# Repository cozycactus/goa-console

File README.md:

# goa-console

A DIY line-level mixing console with 24 or more channels, in the style of the Soundcraft Delta and meant for mixing
hardware synths (goa trance). It is designed in KiCad. Python generates the schematics, which are checked against
intended netlists and simulated in ngspice.

> **Design only, not built.** No board here has been routed, fabricated or powered, so nothing is proven on the bench.
> The external PSU connects to mains, so build it only if you are qualified to work with mains voltages. See
> [Licence](#licence): there is no warranty of any kind.

*3D model built from the placed KiCad boards (`tools/console_3d.py`). Knob caps and panel finish are placeholders.*

## What it is

- **Modules on a motherloom.** Each channel is a Delta Theatre input without the mic stage:
  - one 8 HP × 12U panel with two boards: a 38 × 400 mm main board and a 38 × 43 mm jack board;
  - every module plugs into a daisy-chained 34-way IDC ribbon that uses the Delta's own motherloom pinout, one ribbon
    per wing of 12 strips;
  - the 16 HP master module sits in the centre with both wing headers and the power entry; the four 8 HP group
    modules sit next to it, two on each wing.
- **Channel strip** (spec v5.7):
  - a buffered differential line receiver (OPA1656 followers) and an inverting line gain stage, −15…+15 dB with a
    centre detent;
  - a Ø switch and a sweepable 21–403 Hz high-pass filter (KHN);
  - the Delta's four-band EQ, except that the two swept mid bands are rebuilt as KHN state-variable band-pass
    filters, so a stocked A10K dual pot tunes them;
  - an insert after the EQ, ON (a JFET soft mute that also mutes the pre-fade sends and the direct out) and PFL;
  - a 100 mm fader with a +10 dB post-amp, then pan and routing to L-R, 1-2 and 3-4 through DG413 switches at the
    bus end of each 4K7 summing resistor;
  - six aux sends, with one PRE switch per pair of sends (solder jumpers pick its source: pre-fader or pre-EQ) and a
    DIR switch that makes the aux 6 pot the level of the direct out.
- **Master:**
  - mix summing referenced to a ground-cancel line, each sum followed by a re-inverter;
  - DRV135UA (DRV134 family) balanced outputs with mute relays, plus a power-on mute;
  - mono, PFL and AFL monitoring, 20-LED meters on each side, and the masters for aux 5 and 6.
- **Groups:** each has a sub bus with insert and pan, two stereo returns and an aux master (aux n on group n).
- **Power:** an external supply giving ±17 V at 4 A per rail. Two isolated Mean Well LRS-150-24 modules each feed a
  floating rail with its own LC filter, LM1084 regulator and SCR crowbar. A 7-pin XLR carries the supply to the
  console.

<table>
<tr>
<td></td>
</tr>
<tr>
<td><em>Strip panel print in the Delta's style</em></td>
</tr>
</table>

## Status

| Part | Schematic | Placement | Routing |
|------|-----------|-----------|---------|
| Channel strip (main + jack board) | done, verified, simulated | done | to do |
| Group module ×4 (main + jack board) | done, verified | done | to do |
| Master module (main + jack board) | done, verified | done | to do |
| External PSU | done, verified, simulated | done | to do |
| Test jig (master stub + load board) | done, verified | done | to do |

- **Component placement only.** The boards are generated by the placer and carry no tracks, vias or zones; copper
  routing is done by hand in KiCad (see `AGENTS.md`). Unrouted connections are expected.
- **What the checks show:**
  - parity DRC finds 0 schematic-parity issues on every board;
  - the strip, group and master main boards and both jig boards have 0 DRC violations;
  - the jack boards report only items inside KiCad's NJ6FD-V footprint, and the PSU only 20 known TO-220 silk-edge
    items (the tabs overhang the board edge by design);
  - `python3 tools/check_all.py` runs every check in one go (netlist against intended, pins against footprints, ERC,
    parity DRC, footprint links, route_check, the simulations and the rule tests) and exits non-zero on any failure.
- **Still open:**
  - the bench checks from the master parts review (`docs/reviews/master_parts_review.md`, signed off and applied 2026-10-23):
    re-inverter stability, aux noise, relay release and mains-off timing, PFL tick, meter current-source temperature;
  - check the panel parts against samples:
    - fader pad pattern (1:1 print) and which side of the slot the pins sit;
    - fader law, which the printed dB scale needs;
    - fader-cap fit on the blade;
    - panel stack height;
    - PV cap clearance;
    - knob fit;
  - check the pan pot (ALPS RK09L1240015, chosen 2026-10-25) and the PVA2 latch orientation on samples;
  - route the boards;
  - build the test jig with four routed strips and run its bus tests (`test_jig_spec.md`); some bus decisions wait on
    them;
  - build the 12U frame (`frame/`, FR1-FR3) and the PSU case (`psu_case/`, PC1-PC3: Hammond 1402KV, Fischer SK 47 75 SA).

  The details are in `CLAUDE.md`, "Not done / open" and "Next steps".

## Repository layout

| Path | What |
|------|------|
| `console_architecture.md` | Whole-console architecture (authoritative): bus pinout, grounding, power, op-amp choices |
| `channel_strip_schematic_spec.md`, `docs/reviews/strip_parts_review.md` | Strip component-level spec v5.7 (authoritative), including panel parts and stack (§16); the stability and ratings review behind v4.1 |
| `master_section_spec.md`, `docs/studies/master_panel_study.md`, `docs/reviews/master_parts_review.md` | Master and group modules: functions, parts, panel study, review of the proposed parts |
| `psu_spec.md`, `test_jig_spec.md` | External PSU, test jig |
| `docs/studies/delta_clone_comparison.md`, `docs/studies/strip_panel_study.md` | Why the strip is a Delta clone, why 8 HP × 12U with two pot columns |
| `docs/build/panel_parts_drawings.md`, `docs/build/panel_print.md` | Panel parts against their manufacturers' drawings; the Delta's panel legend system and ours |
| `boards/<name>/` | One folder per KiCad project, nine in all (`channel_strip`, `jack_board`, `group`, `group_jack_board`, `master`, `master_jack_board`, `jig_master_stub`, `jig_load_board`, `psu`). Each holds the generated schematic (`.kicad_sch`, with `*_sheets/` for the hierarchical ones) and placed board (`.kicad_pcb`), `.kicad_pro`, `.kicad_dru`, the netlist `.net`, `_intended.json`, and its own `fp-lib-table` / `sym-lib-table` pointing at the project libraries in the repository root |
| `boards/channel_strip/` | The strip's main board: `channel_strip.kicad_pro` opens it with the schematic. The old v3.1 board is `archive/channel_strip_v3.1.kicad_pcb` |
| `docs/` | The design record: `proposals/`, `reviews/`, `studies/`, `build/` (sourcing, samples, escape plan, panel print), `decisions.md`, `verification_log.md`, `tooling.md`, and `INDEX.md`, the map of all of it |
| `pdf/*.pdf`, `bom/*_BOM.csv` | Schematic PDF and BOM exports; `bom/` also holds the order lists. The netlists (`.net`) and `*_intended.json`, the netlists the schematics are checked against, live in each board's folder |
| `goa-console.pretty/`, `goa-console.3dshapes/`, `goa-console.kicad_sym` | Project footprints (faders, spade tab, PTC), part 3D models (VRML + STEP), symbols |
| `tools/` | Generators, verification (`check_all.py` runs everything), placement engine, routing rules (`netrules.py`), fab outputs (`fab_out.py`), the order list (`order_bom.py`), 3D export and Blender build (below) |
| `sim/` | ngspice decks and Python sims: signal path, EQ, gain stage, mid tuning, routing switch, master mix, meters, mute, PSU |
| `ref/` | **Not in this repository.** It holds third-party documents: the Soundcraft Delta DLX/Theatre schematics, the 200 Delta Technical Manual and User Guide with panel-drawing crops, the Mackie 1604-VLZ service manual and an API 500 spec. The docs still cite them by their `ref/...` paths. The folder is git-ignored, so a local copy stays out of commits |
| `render/` | 3D exports (`*.json`); renders and the `.blend` are generated and git-ignored |
| `CLAUDE.md` | Working notes: rules, current state, one-line decisions, open items; the detail in `docs/INDEX.md` (file map, proposals table), `docs/tooling.md`, `docs/decisions.md` (decisions in full), `docs/verification_log.md` |

## Toolchain

- KiCad 10.0.7: `kicad-cli`, plus its bundled Python 3.9 for `pcbnew` (placement and 3D export).
- Python 3 with a `.venv` holding kiutils 1.4.8 (the schematic generators).
- ngspice 46.
- Blender 5.2, optional (3D model and renders).

On macOS:

```bash
KC=/Applications/KiCad/KiCad.app/Contents/MacOS/kicad-cli
KPY=/Applications/KiCad/KiCad.app/Contents/Frameworks/Python.framework/Versions/3.9/bin/python3
python3 -m venv .venv && .venv/bin/pip install kiutils==1.4.8
```

## Working on it

The schematics are generated: edit the generator, then regenerate and verify every schematic it writes. For the
strip:

```bash
# writes boards/channel_strip/channel_strip.kicad_sch and boards/jack_board/jack_board.kicad_sch
.venv/bin/python tools/gen.py boards/channel_strip/channel_strip.kicad_sch
for s in channel_strip jack_board; do
  $KC sch export netlist -o $s.net $s.kicad_sch
  .venv/bin/python tools/verify.py $s.net ${s}_intended.json
  # symbol pins vs footprint pads
  python3 tools/check_fp.py $s.net
  $KC sch erc --severity-all $s.kicad_sch
done
# strip only: both netlists joined by the ribbon, simulated in ngspice
python3 tools/sim_netlist.py boards/channel_strip/channel_strip.net boards/jack_board/jack_board.net
```

The whole console (24 strips, 4 groups and the master, each with its jack board, on the ribbon) is simulated from the
generated netlists with `python3 tools/sim_console.py` (108 checks, a little over a minute; `--list` names them). It covers
levels, routing, mutes, PFL, returns, EXT, crosstalk, ground currents and noise. Regenerate the netlists first.

The other generators work the same way:

| Generator | Writes |
|-----------|--------|
| `gen_group.py boards/group/group.kicad_sch` | group, group_jack_board |
| `gen_master.py boards/master/master.kicad_sch` | master, master_jack_board |
| `gen_psu.py` (no argument) | psu |
| `gen_jig.py` (no argument) | jig_master_stub, jig_load_board |

Run the export / verify / check_fp / ERC steps for each schematic in the right-hand column.

Simulations: each deck in `sim/` runs its own analyses, e.g. `ngspice -b sim/strip_v4.cir` (the v4.0 strip model; the
current strip is checked from its netlist by `sim_netlist.py`, 45 checks). `python3 sim/mid_tuning.py 10e3` compares the
mid-band tunings for a given pot value (the 2026-10-22 tuning; the v5.5 ranges come from `sim/review/eqmid/measure.py`).

Placement only. The strip, group and master main boards have four layers, with a solid ground plane and a ground fill
inside (`docs/studies/layer_study.md`); every other board has two. Each script refuses to overwrite a board that
already has routing:

```bash
# strip main board + jack board
tools/build_strip_pcb.sh
# group, master (~3 min) and their jack boards
$KPY tools/place_group.py
$KPY tools/place_master.py
$KPY tools/place_jig.py
$KPY tools/place_psu.py
```

Each run prints a placement report: decoupler-to-supply-pin distances and the reach of high-impedance input
networks. Every board is its schematic's project board, so parity DRC runs in place
(`$KC pcb drc --schematic-parity --severity-all X.kicad_pcb`). After any re-placement or netlist change, re-run
`$KPY tools/netrules.py` (net classes and the `.kicad_dru` rules). `python3 tools/fab_out.py BOARD` writes Gerbers,
drills, position file and BOM to `fab/BOARD/` once a board is routed; `python3 tools/order_bom.py` builds the
console-wide order list from the BOMs.

Part models and the 3D console:

```bash
# part models vs footprints; writes goa-console.3dshapes
python3 tools/models3d/check.py --wrl --kicad
# placed boards to JSON, one file per module
$KPY tools/export_3d.py boards/channel_strip/channel_strip.kicad_pcb boards/jack_board/jack_board.kicad_pcb > render/strip.json
$KPY tools/export_3d.py boards/group/group.kicad_pcb boards/group_jack_board/group_jack_board.kicad_pcb > render/group.json
$KPY tools/export_3d.py boards/master/master.kicad_pcb boards/master_jack_board/master_jack_board.kicad_pcb > render/master.json
# builds render/goa_console.blend and renders the views
BLENDER=/Applications/Blender.app/Contents/MacOS/Blender
$BLENDER -b --factory-startup --python tools/console_3d.py -- render
```

## Conventions

- **Generated files are not edited by hand:** schematics, boards, footprints and 3D models. Change the generator
  (`tools/gen*.py`, `tools/master_lib.py`, `tools/place_*.py`, `tools/footprints.py`, `tools/models3d/`) and
  regenerate.
- **Decisions are recorded with their date** in `docs/decisions_summary.md` (one line each), `docs/decisions.md` (in full) and the specs. Changing one is a
  deliberate step, not a side effect.
- **The Delta schematics are the circuit reference.** Where this design departs from them, the reason is in
  `docs/studies/delta_clone_comparison.md` or the spec.

## Licence

Copyright 2026 Ruslan Migirov. Licensed under the [CERN Open Hardware Licence Version 2, Strongly Reciprocal](LICENSE)
(`SPDX-License-Identifier: CERN-OHL-S-2.0`). It covers the whole repository including `tools/`, because the generators
there hold the design itself: the netlists, the schematic drawings and the placement. The design is provided as is, with
no warranty of any kind.

Not covered by that licence:

- SPICE model parameters under `sim/` that come from component manufacturers remain theirs.
- Standard KiCad library footprints and 3D models used by the boards stay under the KiCad libraries' own licence.

Soundcraft, Delta, Mackie and API are trademarks of their respective owners. This project is not affiliated with or
endorsed by any of them.

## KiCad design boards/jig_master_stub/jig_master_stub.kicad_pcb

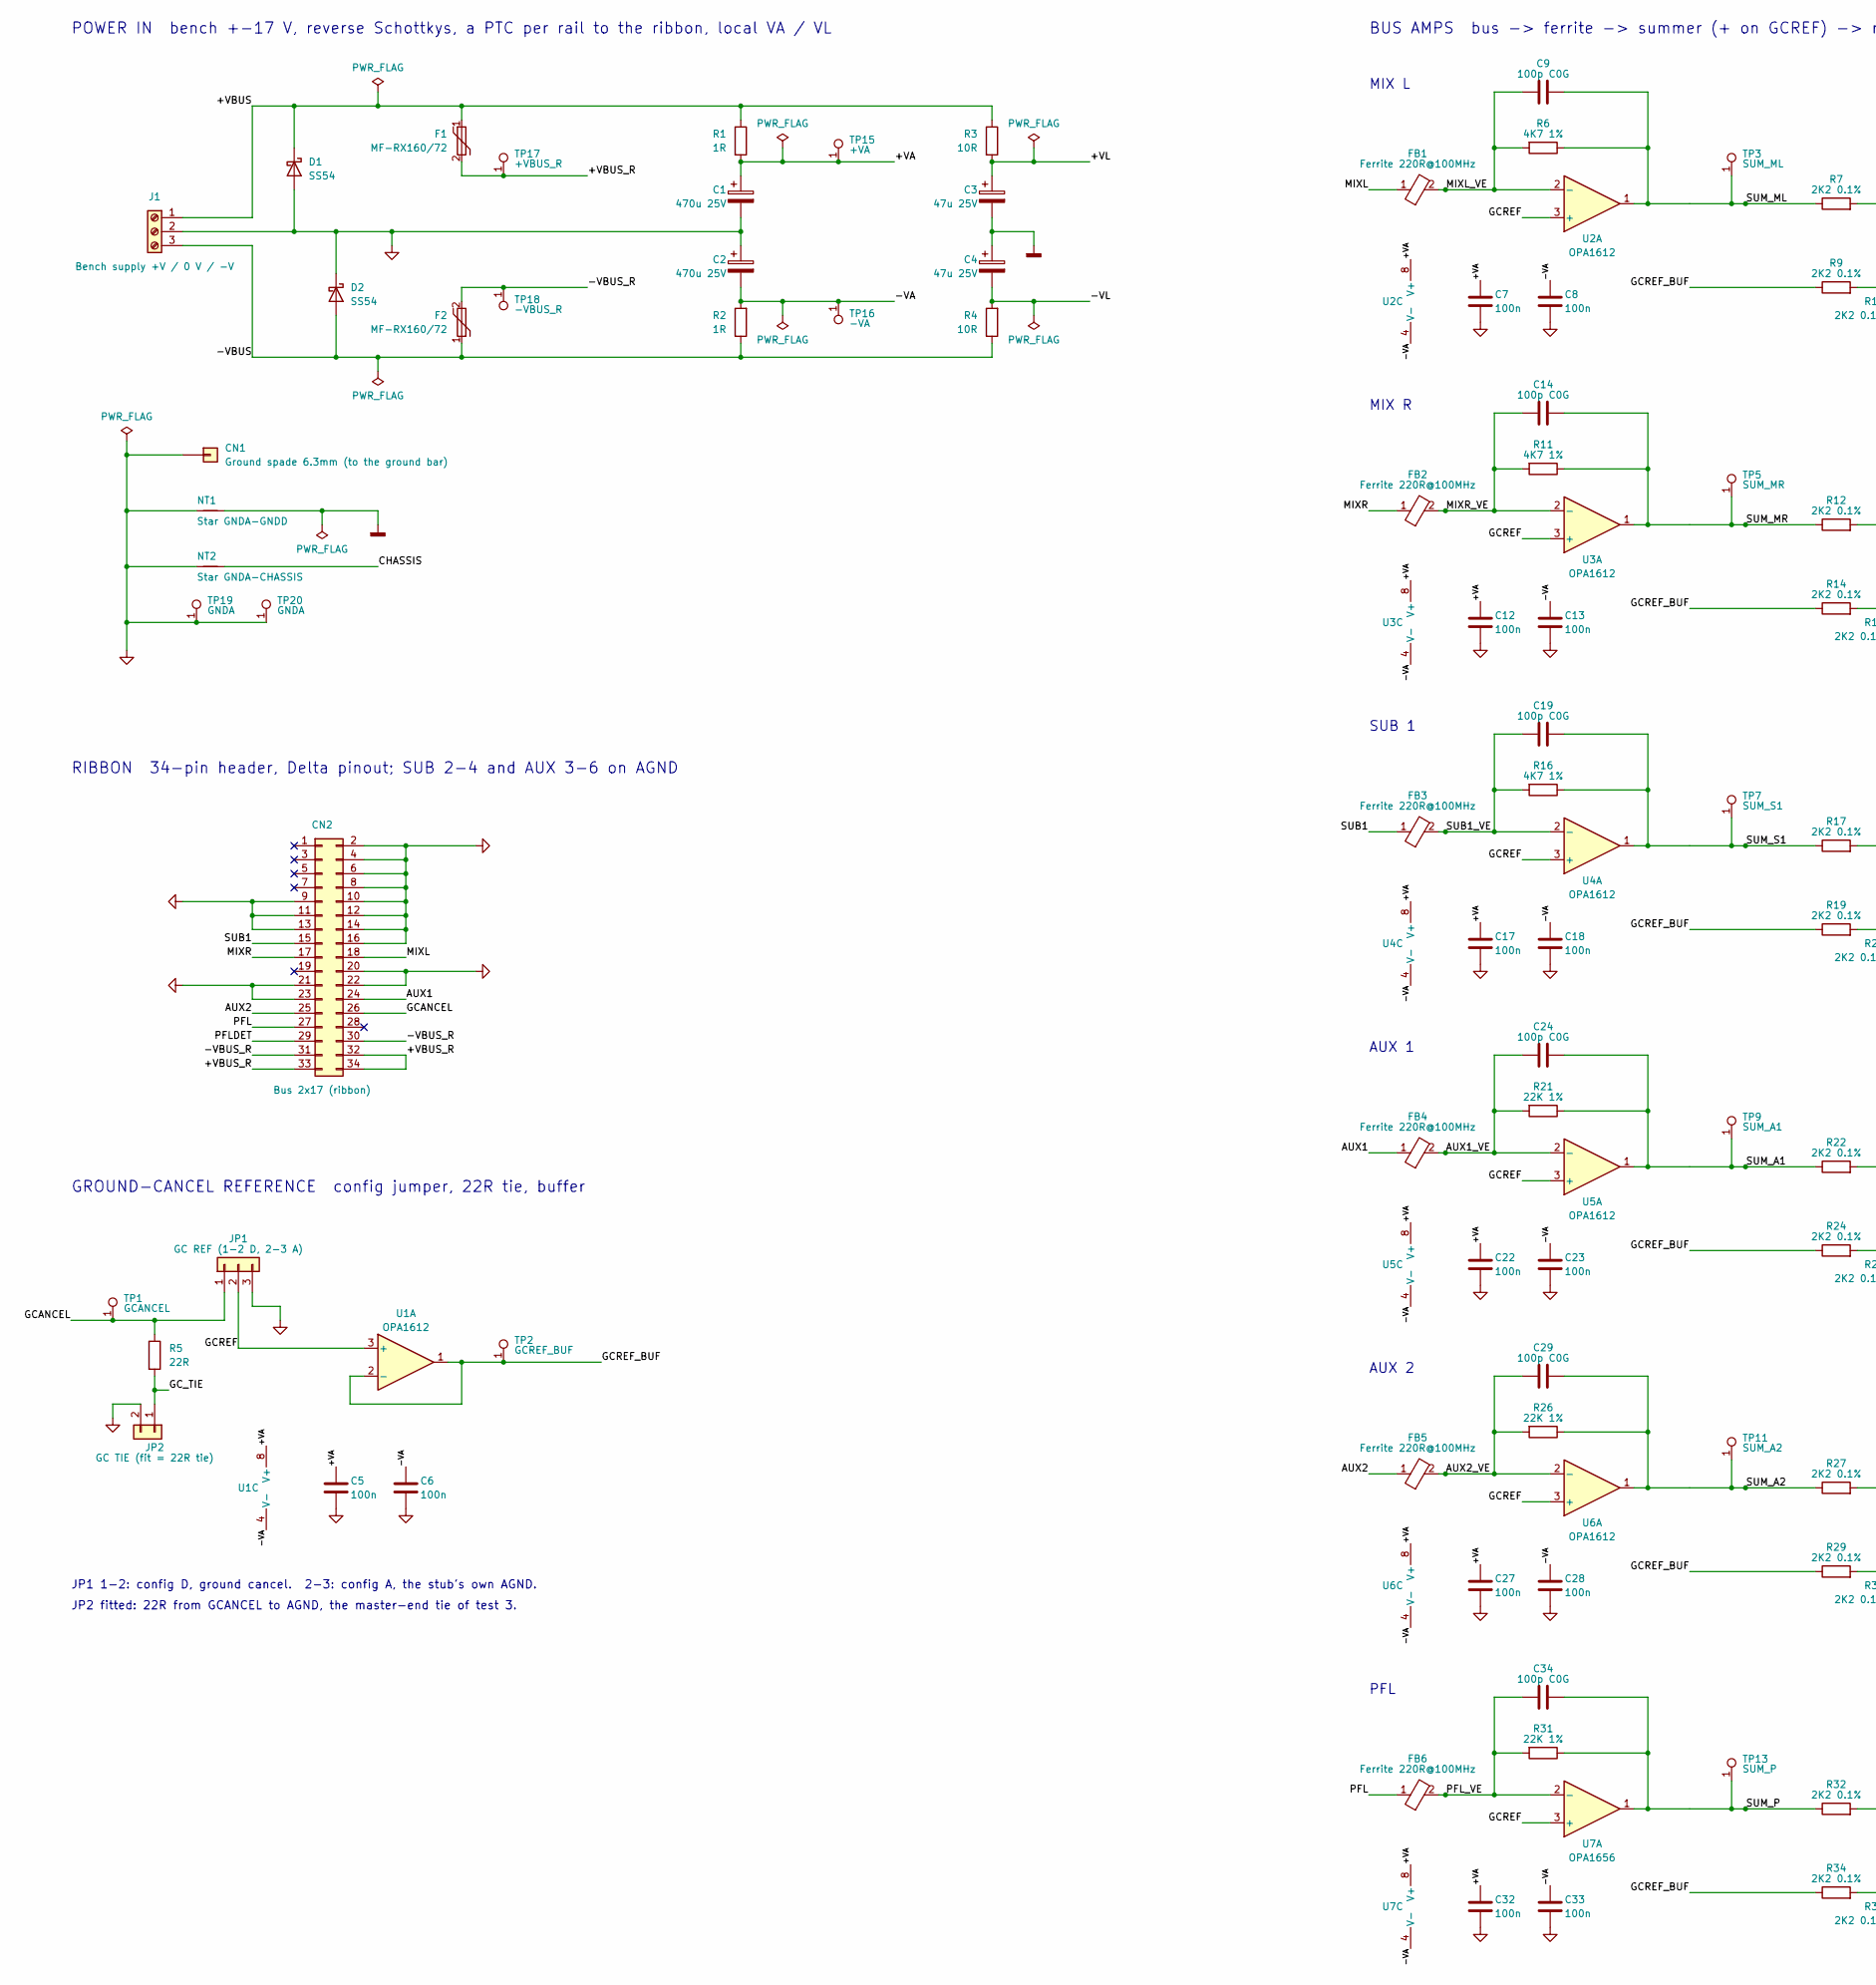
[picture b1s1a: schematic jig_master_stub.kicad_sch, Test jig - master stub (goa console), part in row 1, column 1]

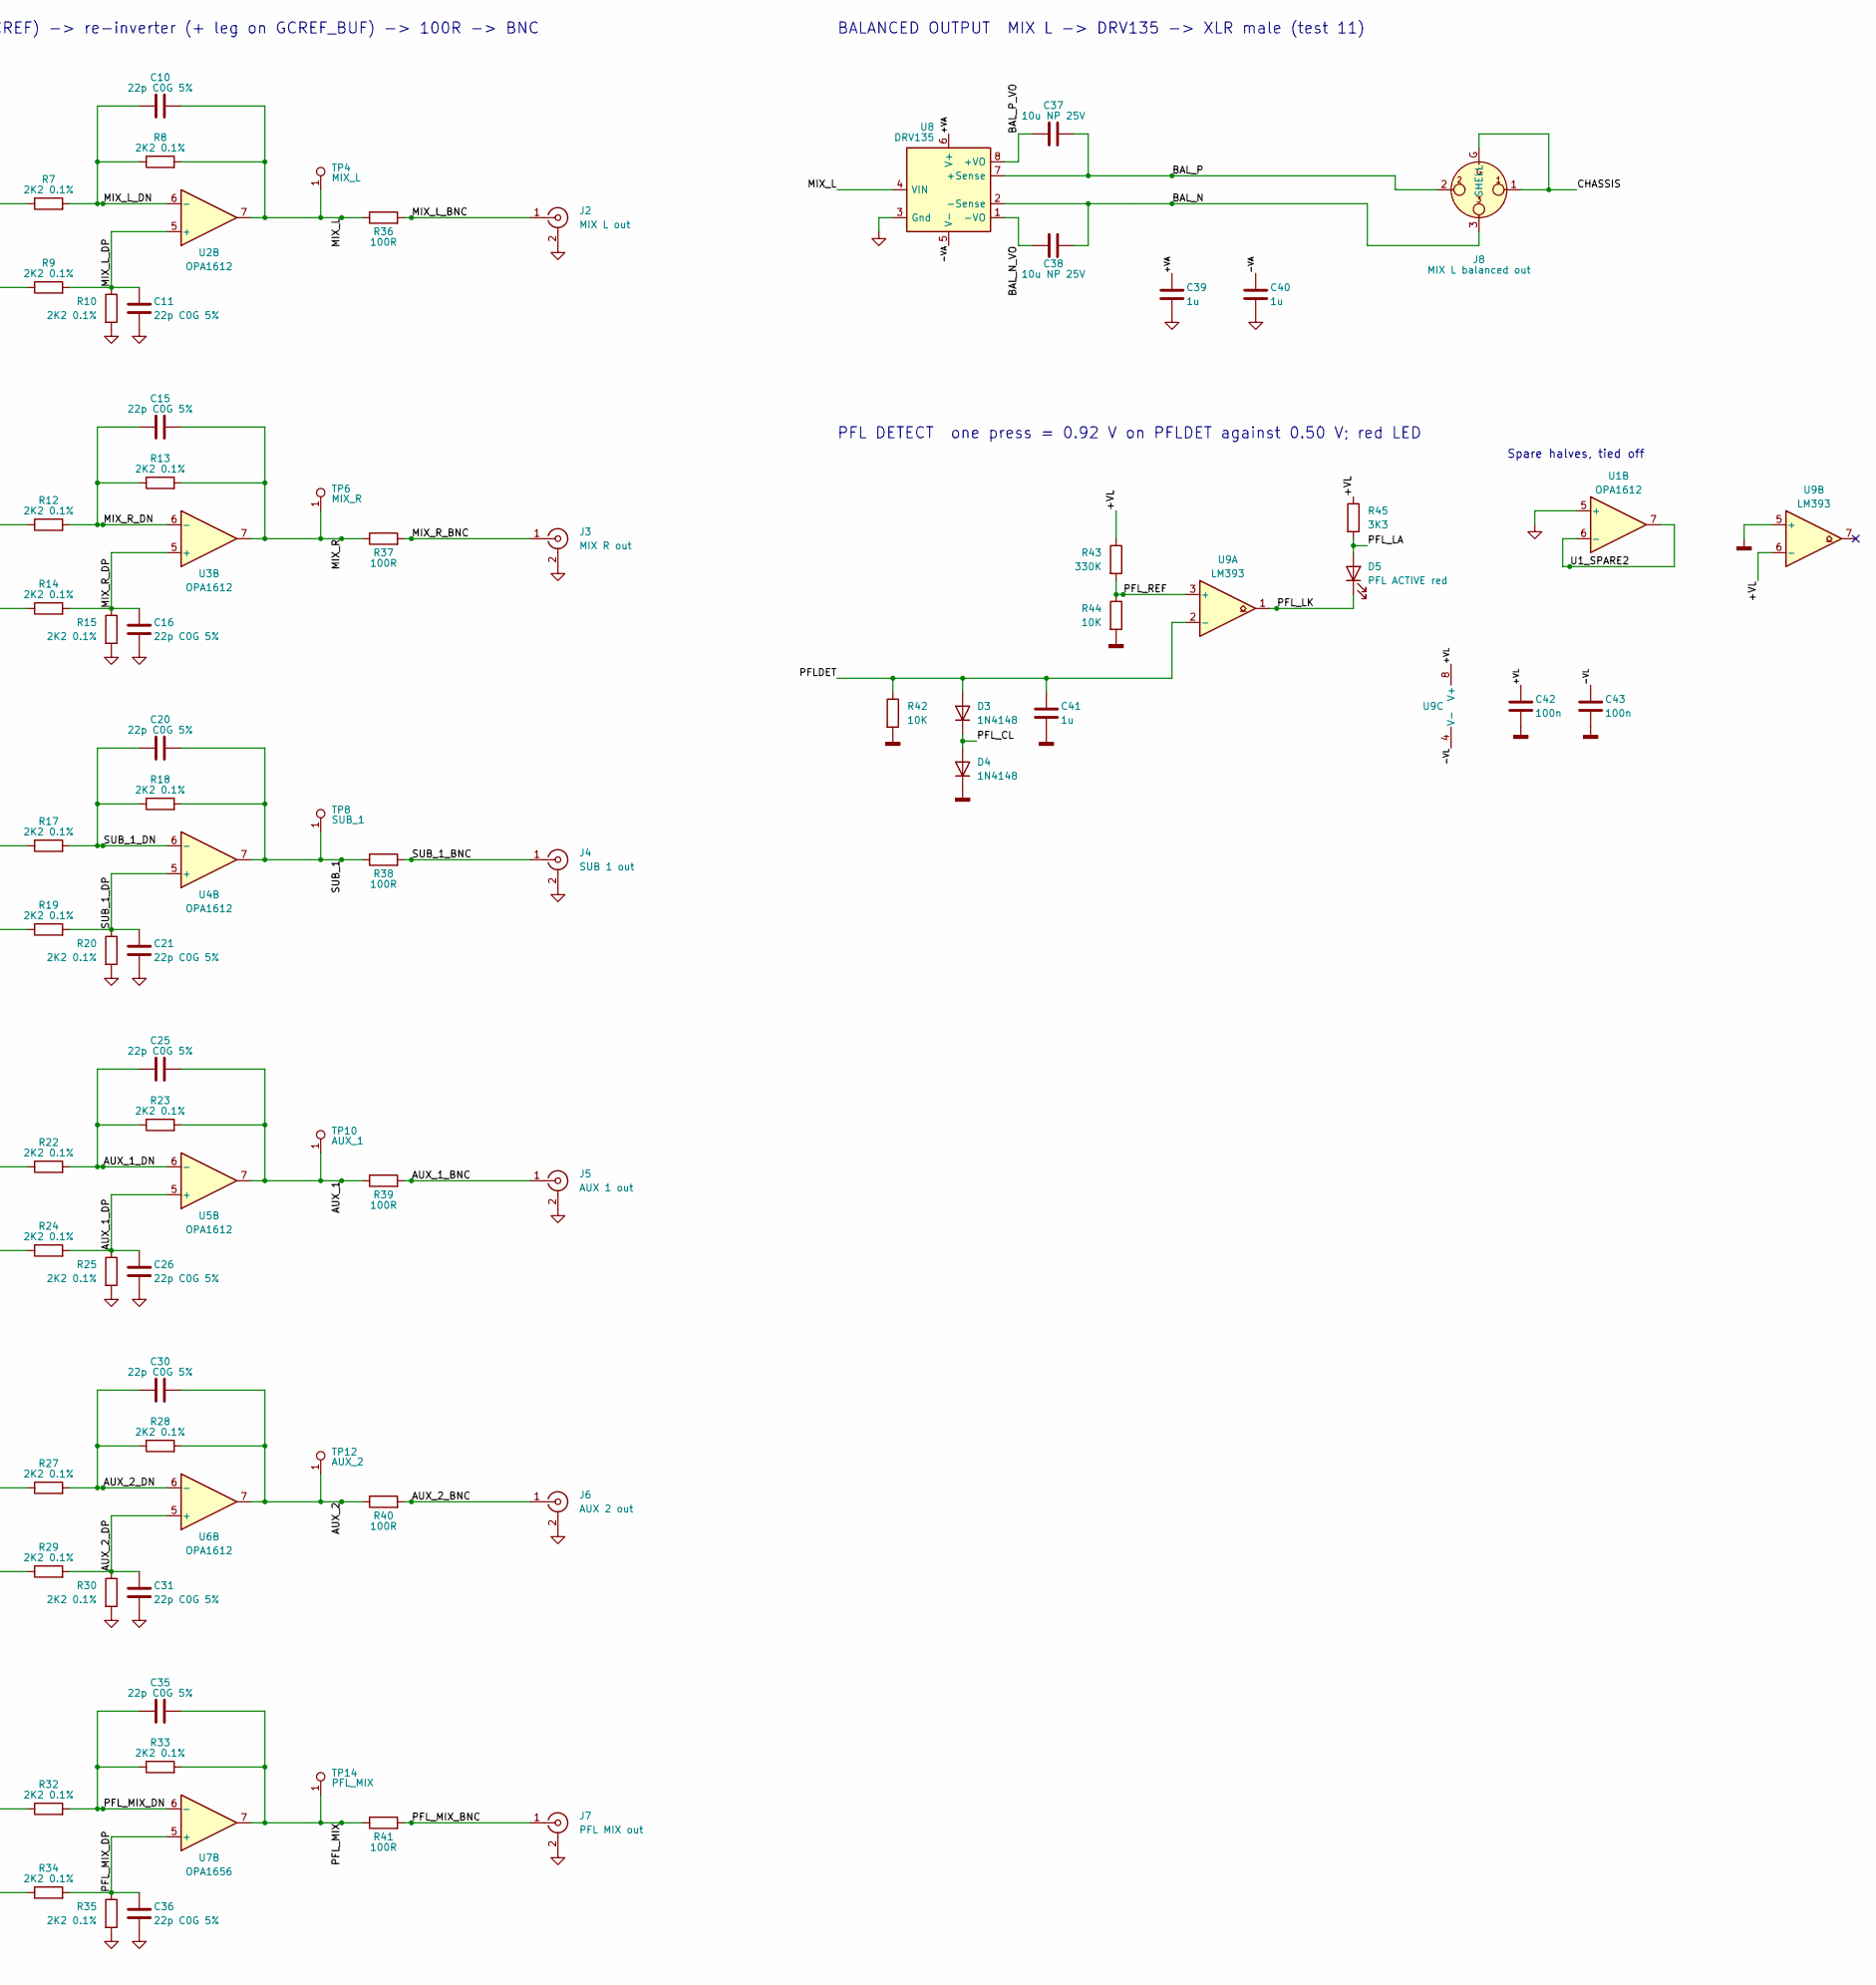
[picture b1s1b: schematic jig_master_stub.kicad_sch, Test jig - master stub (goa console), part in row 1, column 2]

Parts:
C1, C2: 470u 25V; CP_Radial_D10.0mm_P5.00mm; MPN Nichicon UPW1E471MPD
C3, C4: 47u 25V; CP_Radial_D8.0mm_P3.50mm; MPN Nichicon UPW1J470MPD (63V)
C5, C6, C7, C8, C12, C13, C17, C18, C22, C23, C27, C28, C32, C33, C42, C43: 100n; C_0805_2012Metric; MPN Samsung CL21B104KBCNNNC (X7R 50V)
C9, C14, C19, C24, C29, C34: 100p C0G; C_0805_2012Metric; MPN KEMET C0805C101J5GACTU
C10, C11, C15, C16, C20, C21, C25, C26, C30, C31, C35, C36: 22p C0G 5%; C_0805_2012Metric; MPN KEMET C0805C220J5GACTU
C37, C38: 10u NP 25V; CP_Radial_D5.0mm_P2.00mm; MPN Panasonic ECE-A1EN100U
C39, C40, C41: 1u; C_1206_3216Metric; MPN Samsung CL31B105KBHNNNE (X7R 50V)
CN1: Ground spade 6.3mm (to the ground bar); Keystone_1287-ST_FastOn_Tab_6.35mm; MPN Keystone 1287-ST
CN2: Bus 2x17 (ribbon); IDC-Header_2x17_P2.54mm_Vertical; MPN Wurth 61203421621 (2x17 box header)
D1, D2: SS54; D_SMC; MPN Diodes B540C-13-F (SS54 class, SMC 40 V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
D3, D4: 1N4148; D_DO-35_SOD27_P7.62mm_Horizontal; MPN Vishay 1N4148-TAP
D5: PFL ACTIVE red; LED_D3.0mm; MPN Kingbright WP710A10ID
F1, F2: MF-RX160/72; Fuse_Bourns_MF-RX160-72_Radial_P5.08mm; MPN Bourns MF-RX160/72-0
FB1, FB2, FB3, FB4, FB5, FB6: Ferrite 220R@100MHz; L_0805_2012Metric; MPN Murata BLM21PG221SN1D
J1: Bench supply +V / 0 V / -V; TerminalBlock_Phoenix_MKDS-1,5-3-5.08_1x03_P5.08mm_Horizont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; MPN Phoenix 1715734 MKDS 1,5/3-5,08
J2: MIX L out; BNC_Amphenol_B6252HB-NPP3G-50_Horizontal; MPN Amphenol B6252HB-NPP3G-50
J3: MIX R out; BNC_Amphenol_B6252HB-NPP3G-50_Horizontal; MPN Amphenol B6252HB-NPP3G-50
J4: SUB 1 out; BNC_Amphenol_B6252HB-NPP3G-50_Horizontal; MPN Amphenol B6252HB-NPP3G-50
J5: AUX 1 out; BNC_Amphenol_B6252HB-NPP3G-50_Horizontal; MPN Amphenol B6252HB-NPP3G-50
J6: AUX 2 out; BNC_Amphenol_B6252HB-NPP3G-50_Horizontal; MPN Amphenol B6252HB-NPP3G-50
J7: PFL MIX out; BNC_Amphenol_B6252HB-NPP3G-50_Horizontal; MPN Amphenol B6252HB-NPP3G-50
J8: MIX L balanced out; Jack_XLR_Neutrik_NC3MAH_Horizontal; MPN Neutrik NC3MAH
JP1: GC REF (1-2 D, 2-3 A); PinHeader_1x03_P2.54mm_Vertical; MPN 2.54 mm header + shunt
JP2: GC TIE (fit = 22R tie); PinHeader_1x02_P2.54mm_Vertical; MPN 2.54 mm header + shunt
NT1: Star GNDA-GNDD; NetTie-2_SMD_Pad0.5mm
NT2: Star GNDA-CHASSIS; NetTie-2_SMD_Pad0.5mm
R1, R2: 1R; R_0805_2012Metric; MPN Panasonic ERJ-P06J1R0V
R3, R4: 10R; R_0805_2012Metric
R5: 22R; R_0805_2012Metric
R6, R11, R16: 4K7 1%; R_0805_2012Metric
R7, R8, R9, R10, R12, R13, R14, R15, R17, R18, R19, R20, R22, R23, R24, R25, R27, R28, R29, R30, R32, R33, R34, R35: 2K2 0.1%; R_0805_2012Metric; MPN Panasonic ERA-6AEB222V
R21, R26, R31: 22K 1%; R_0805_2012Metric
R36, R37, R38, R39, R40, R41: 100R; R_0805_2012Metric
R42, R44: 10K; R_0805_2012Metric
R43: 330K; R_0805_2012Metric
R45: 3K3; R_0805_2012Metric; MPN Panasonic ERJ-P06J332V
TP1: GCANCEL; TestPoint_Keystone_5010-5014_Multipurpose; MPN Keystone 5010
TP2: GCREF_BUF; TestPoint_Keystone_5010-5014_Multipurpose; MPN Keystone 5010
TP3: SUM_ML; TestPoint_Keystone_5010-5014_Multipurpose; MPN Keystone 5010
TP4: MIX_L; TestPoint_Keystone_5010-5014_Multipurpose; MPN Keystone 5010
TP5: SUM_MR; TestPoint_Keystone_5010-5014_Multipurpose; MPN Keystone 5010
TP6: MIX_R; TestPoint_Keystone_5010-5014_Multipurpose; MPN Keystone 5010
TP7: SUM_S1; TestPoint_Keystone_5010-5014_Multipurpose; MPN Keystone 5010
TP8: SUB_1; TestPoint_Keystone_5010-5014_Multipurpose; MPN Keystone 5010
TP9: SUM_A1; TestPoint_Keystone_5010-5014_Multipurpose; MPN Keystone 5010
TP10: AUX_1; TestPoint_Keystone_5010-5014_Multipurpose; MPN Keystone 5010
TP11: SUM_A2; TestPoint_Keystone_5010-5014_Multipurpose; MPN Keystone 5010
TP12: AUX_2; TestPoint_Keystone_5010-5014_Multipurpose; MPN Keystone 5010
TP13: SUM_P; TestPoint_Keystone_5010-5014_Multipurpose; MPN Keystone 5010
TP14: PFL_MIX; TestPoint_Keystone_5010-5014_Multipurpose; MPN Keystone 5010
TP15: +VA; TestPoint_Keystone_5010-5014_Multipurpose; MPN Keystone 5010
TP16: -VA; TestPoint_Keystone_5010-5014_Multipurpose; MPN Keystone 5010
TP17: +VBUS_R; TestPoint_Keystone_5010-5014_Multipurpose; MPN Keystone 5010
TP18: -VBUS_R; TestPoint_Keystone_5010-5014_Multipurpose; MPN Keystone 5010
TP19, TP20: GNDA; TestPoint_Keystone_5010-5014_Multipurpose; MPN Keystone 5010
U1, U2, U3, U4, U5, U6: OPA1612; SOIC-8_3.9x4.9mm_P1.27mm; MPN TI OPA1612AIDR
U7: OPA1656; SOIC-8_3.9x4.9mm_P1.27mm; MPN TI OPA1656IDR
U8: DRV135; SOIC-8_3.9x4.9mm_P1.27mm; MPN TI DRV135UA
U9: LM393; SOIC-8_3.9x4.9mm_P1.27mm; MPN TI LM393BIDR

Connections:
/+VA: C1.1, C5.1, C7.1, C12.1, C17.1, C22.1, C27.1, C32.1, C39.1, R1.2, TP15.1, U1.8 (V+), U2.8 (V+), U3.8 (V+), U4.8 (V+), U5.8 (V+), U6.8 (V+), U7.8 (V+), U8.6 (V+)
/+VBUS: D1.1 (K), F1.1, J1.1, R1.1, R3.1
/+VBUS_R: CN2.32, CN2.33, CN2.34, F1.2, TP17.1
/+VL: C3.1, C42.1, R3.2, R43.1, R45.1, U9.6 (-), U9.8 (V+)
/-VA: C2.2, C6.2, C8.2, C13.2, C18.2, C23.2, C28.2, C33.2, C40.2, R2.2, TP16.1, U1.4 (V-), U2.4 (V-), U3.4 (V-), U4.4 (V-), U5.4 (V-), U6.4 (V-), U7.4 (V-), U8.5 (V-)
/-VBUS: D2.2 (A), F2.1, J1.3, R2.1, R4.1
/-VBUS_R: CN2.30, CN2.31, F2.2, TP18.1
/-VL: C4.2, C43.2, R4.2, U9.4 (V-)
/AUX1: CN2.24, FB4.1
/AUX1_VE: C24.2, FB4.2, R21.2, U5.2 (-)
/AUX2: CN2.25, FB5.1
/AUX2_VE: C29.2, FB5.2, R26.2, U6.2 (-)
/AUX_1: C25.1, R23.2, R39.1, TP10.1, U5.7
/AUX_1_BNC: J5.1 (In), R39.2
/AUX_1_DN: C25.2, R22.2, R23.1, U5.6 (-)
/AUX_1_DP: C26.1, R24.2, R25.1, U5.5 (+)
/AUX_2: C30.1, R28.2, R40.1, TP12.1, U6.7
/AUX_2_BNC: J6.1 (In), R40.2
/AUX_2_DN: C30.2, R27.2, R28.1, U6.6 (-)
/AUX_2_DP: C31.1, R29.2, R30.1, U6.5 (+)
/BAL_N: C38.2, J8.3, U8.2 (-Sense)
/BAL_N_VO: C38.1, U8.1 (-VO)
/BAL_P: C37.2, J8.2, U8.7 (+Sense)
/BAL_P_VO: C37.1, U8.8 (+VO)
/CHASSIS: J8.1, J8.G (SHELL), NT2.2
/GCANCEL: CN2.26, JP1.1, R5.1, TP1.1
/GCREF: JP1.2, U1.3 (+), U2.3 (+), U3.3 (+), U4.3 (+), U5.3 (+), U6.3 (+), U7.3 (+)
/GCREF_BUF: R9.1, R14.1, R19.1, R24.1, R29.1, R34.1, TP2.1, U1.1, U1.2 (-)
/GC_TIE: JP2.1, R5.2
/MIXL: CN2.18, FB1.1
/MIXL_VE: C9.2, FB1.2, R6.2, U2.2 (-)
/MIXR: CN2.17, FB2.1
/MIXR_VE: C14.2, FB2.2, R11.2, U3.2 (-)
/MIX_L: C10.1, R8.2, R36.1, TP4.1, U2.7, U8.4 (VIN)
/MIX_L_BNC: J2.1 (In), R36.2
/MIX_L_DN: C10.2, R7.2, R8.1, U2.6 (-)
/MIX_L_DP: C11.1, R9.2, R10.1, U2.5 (+)
/MIX_R: C15.1, R13.2, R37.1, TP6.1, U3.7
/MIX_R_BNC: J3.1 (In), R37.2
/MIX_R_DN: C15.2, R12.2, R13.1, U3.6 (-)
/MIX_R_DP: C16.1, R14.2, R15.1, U3.5 (+)
/PFL: CN2.27, FB6.1
/PFLDET: C41.1, CN2.29, D3.2 (A), R42.1, U9.2 (-)
/PFL_CL: D3.1 (K), D4.2 (A)
/PFL_LA: D5.2 (A), R45.2
/PFL_LK: D5.1 (K), U9.1
/PFL_MIX: C35.1, R33.2, R41.1, TP14.1, U7.7
/PFL_MIX_BNC: J7.1 (In), R41.2
/PFL_MIX_DN: C35.2, R32.2, R33.1, U7.6 (-)
/PFL_MIX_DP: C36.1, R34.2, R35.1, U7.5 (+)
/PFL_REF: R43.2, R44.1, U9.3 (+)
/PFL_VE: C34.2, FB6.2, R31.2, U7.2 (-)
/SUB1: CN2.15, FB3.1
/SUB1_VE: C19.2, FB3.2, R16.2, U4.2 (-)
/SUB_1: C20.1, R18.2, R38.1, TP8.1, U4.7
/SUB_1_BNC: J4.1 (In), R38.2
/SUB_1_DN: C20.2, R17.2, R18.1, U4.6 (-)
/SUB_1_DP: C21.1, R19.2, R20.1, U4.5 (+)
/SUM_A1: C24.1, R21.1, R22.1, TP9.1, U5.1
/SUM_A2: C29.1, R26.1, R27.1, TP11.1, U6.1
/SUM_ML: C9.1, R6.1, R7.1, TP3.1, U2.1
/SUM_MR: C14.1, R11.1, R12.1, TP5.1, U3.1
/SUM_P: C34.1, R31.1, R32.1, TP13.1, U7.1
/SUM_S1: C19.1, R16.1, R17.1, TP7.1, U4.1
/U1_SPARE2: U1.6 (-), U1.7
GNDA: C1.2, C2.1, C5.2, C6.1, C7.2, C8.1, C11.2, C12.2, C13.1, C16.2, C17.2, C18.1, C21.2, C22.2, C23.1, C26.2, C27.2, C28.1, C31.2, C32.2, C33.1, C36.2, C39.2, C40.1, CN1.1, CN2.2, CN2.4, CN2.6, CN2.8, CN2.9, CN2.10, CN2.11, CN2.12, CN2.13, CN2.14, CN2.16, CN2.20, CN2.21, CN2.22, CN2.23, D1.2 (A), D2.1 (K), J1.2, J2.2 (Ext), J3.2 (Ext), J4.2 (Ext), J5.2 (Ext), J6.2 (Ext), J7.2 (Ext), JP1.3, JP2.2, NT1.1, NT2.1, R10.2, R15.2, R20.2, R25.2, R30.2, R35.2, TP19.1, TP20.1, U1.5 (+), U8.3 (Gnd)
GNDD: C3.2, C4.1, C41.2, C42.2, C43.1, D4.1 (K), NT1.2, R42.2, R44.2, U9.5 (+)

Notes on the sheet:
POWER IN bench +-17 V, reverse Schottkys, a PTC per rail to the ribbon, local VA / VL
RIBBON 34-pin header, Delta pinout; SUB 2-4 and AUX 3-6 on AGND
GROUND-CANCEL REFERENCE config jumper, 22R tie, buffer
JP1 1-2: config D, ground cancel. 2-3: config A, the stub's own AGND.
JP2 fitted: 22R from GCANCEL to AGND, the master-end tie of test 3.
BUS AMPS bus -> ferrite -> summer (+ on GCREF) -> re-inverter (+ leg on GCREF_BUF) -> 100R -> BNC
MIX L
MIX R
SUB 1
AUX 1
AUX 2
PFL
BALANCED OUTPUT MIX L -> DRV135 -> XLR male (test 11)
PFL DETECT one press = 0.92 V on PFLDET against 0.50 V; red LED
Spare halves, tied off

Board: 2 copper layers, 148 parts (0 on the bottom side), 67 nets, no tracks yet.

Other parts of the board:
H1, H2, H3, H4: M3 standoff; MountingHole_3.2mm_M3

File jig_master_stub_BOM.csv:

"Qty","Value","Footprint","MPN","DNP","References"
"2","470u 25V","Capacitor_THT:CP_Radial_D10.0mm_P5.00mm","Nichicon UPW1E471MPD","","C1 C2"
"2","47u 25V","Capacitor_THT:CP_Radial_D8.0mm_P3.50mm","Nichicon UPW1J470MPD (63V)","","C3 C4"
"16","100n","Capacitor_SMD:C_0805_2012Metric","Samsung CL21B104KBCNNNC (X7R 50V)","","C5 C6 C7 C8 C12 C13 C17 C18 C22 C23 C27 C28 C32 C33 C42 C43"
"6","100p C0G","Capacitor_SMD:C_0805_2012Metric","KEMET C0805C101J5GACTU","","C9 C14 C19 C24 C29 C34"
"12","22p C0G 5%","Capacitor_SMD:C_0805_2012Metric","KEMET C0805C220J5GACTU","","C10 C11 C15 C16 C20 C21 C25 C26 C30 C31 C35 C36"
"2","10u NP 25V","Capacitor_THT:CP_Radial_D5.0mm_P2.00mm","Panasonic ECE-A1EN100U","","C37 C38"
"3","1u","Capacitor_SMD:C_1206_3216Metric","Samsung CL31B105KBHNNNE (X7R 50V)","","C39 C40 C41"
"1","Ground spade 6.3mm (to the ground bar)","goa-console:Keystone_1287-ST_FastOn_Tab_6.35mm","Keystone 1287-ST","","CN1"
"1","Bus 2x17 (ribbon)","Connector_IDC:IDC-Header_2x17_P2.54mm_Vertical","Wurth 61203421621 (2x17 box header)","","CN2"
"2","SS54","Diode_SMD:D_SMC","Diodes B540C-13-F (SS54 class, SMC 40 V 5 A)","","D1 D2"
"2","1N4148","Diode_THT:D_DO-35_SOD27_P7.62mm_Horizontal","Vishay 1N4148-TAP","","D3 D4"
"1","PFL ACTIVE red","LED_THT:LED_D3.0mm","Kingbright WP710A10ID","","D5"
"2","MF-RX160/72","goa-console:Fuse_Bourns_MF-RX160-72_Radial_P5.08mm","Bourns MF-RX160/72-0","","F1 F2"
"6","Ferrite 220R@100MHz","Inductor_SMD:L_0805_2012Metric","Murata BLM21PG221SN1D","","FB1 FB2 FB3 FB4 FB5 FB6"
"1","Bench supply +V / 0 V / -V","TerminalBlock_Phoenix:TerminalBlock_Phoenix_MKDS-1,5-3-5.08_1x03_P5.08mm_Horizontal","Phoenix 1715734 MKDS 1,5/3-5,08","","J1"
"1","MIX L out","Connector_Coaxial:BNC_Amphenol_B6252HB-NPP3G-50_Horizontal","Amphenol B6252HB-NPP3G-50","","J2"
"1","MIX R out","Connector_Coaxial:BNC_Amphenol_B6252HB-NPP3G-50_Horizontal","Amphenol B6252HB-NPP3G-50","","J3"
"1","SUB 1 out","Connector_Coaxial:BNC_Amphenol_B6252HB-NPP3G-50_Horizontal","Amphenol B6252HB-NPP3G-50","","J4"
"1","AUX 1 out","Connector_Coaxial:BNC_Amphenol_B6252HB-NPP3G-50_Horizontal","Amphenol B6252HB-NPP3G-50","","J5"
"1","AUX 2 out","Connector_Coaxial:BNC_Amphenol_B6252HB-NPP3G-50_Horizontal","Amphenol B6252HB-NPP3G-50","","J6"
"1","PFL MIX out","Connector_Coaxial:BNC_Amphenol_B6252HB-NPP3G-50_Horizontal","Amphenol B6252HB-NPP3G-50","","J7"
"1","MIX L balanced out","Connector_Audio:Jack_XLR_Neutrik_NC3MAH_Horizontal","Neutrik NC3MAH","","J8"
"1","GC REF (1-2 D, 2-3 A)","Connector_PinHeader_2.54mm:PinHeader_1x03_P2.54mm_Vertical","2.54 mm header + shunt","","JP1"
"1","GC TIE (fit = 22R tie)","Connector_PinHeader_2.54mm:PinHeader_1x02_P2.54mm_Vertical","2.54 mm header + shunt","","JP2"
"2","1R","Resistor_SMD:R_0805_2012Metric","Panasonic ERJ-P06J1R0V","","R1 R2"
"2","10R","Resistor_SMD:R_0805_2012Metric","","","R3 R4"
"1","22R","Resistor_SMD:R_0805_2012Metric","","","R5"
"3","4K7 1%","Resistor_SMD:R_0805_2012Metric","","","R6 R11 R16"
"24","2K2 0.1%","Resistor_SMD:R_0805_2012Metric","Panasonic ERA-6AEB222V","","R7 R8 R9 R10 R12 R13 R14 R15 R17 R18 R19 R20 R22 R23 R24 R25 R27 R28 R29 R30 R32 R33 R34 R35"
"3","22K 1%","Resistor_SMD:R_0805_2012Metric","","","R21 R26 R31"
"6","100R","Resistor_SMD:R_0805_2012Metric","","","R36 R37 R38 R39 R40 R41"
"2","10K","Resistor_SMD:R_0805_2012Metric","","","R42 R44"
"1","330K","Resistor_SMD:R_0805_2012Metric","","","R43"
"1","3K3","Resistor_SMD:R_0805_2012Metric","Panasonic ERJ-P06J332V","","R45"
"1","GCANCEL","TestPoint:TestPoint_Keystone_5010-5014_Multipurpose","Keystone 5010","","TP1"
"1","GCREF_BUF","TestPoint:TestPoint_Keystone_5010-5014_Multipurpose","Keystone 5010","","TP2"
"1","SUM_ML","TestPoint:TestPoint_Keystone_5010-5014_Multipurpose","Keystone 5010","","TP3"
"1","MIX_L","TestPoint:TestPoint_Keystone_5010-5014_Multipurpose","Keystone 5010","","TP4"
"1","SUM_MR","TestPoint:TestPoint_Keystone_5010-5014_Multipurpose","Keystone 5010","","TP5"
"1","MIX_R","TestPoint:TestPoint_Keystone_5010-5014_Multipurpose","Keystone 5010","","TP6"
"1","SUM_S1","TestPoint:TestPoint_Keystone_5010-5014_Multipurpose","Keystone 5010","","TP7"
"1","SUB_1","TestPoint:TestPoint_Keystone_5010-5014_Multipurpose","Keystone 5010","","TP8"
"1","SUM_A1","TestPoint:TestPoint_Keystone_5010-5014_Multipurpose","Keystone 5010","","TP9"
"1","AUX_1","TestPoint:TestPoint_Keystone_5010-5014_Multipurpose","Keystone 5010","","TP10"
"1","SUM_A2","TestPoint:TestPoint_Keystone_5010-5014_Multipurpose","Keystone 5010","","TP11"
"1","AUX_2","TestPoint:TestPoint_Keystone_5010-5014_Multipurpose","Keystone 5010","","TP12"
"1","SUM_P","TestPoint:TestPoint_Keystone_5010-5014_Multipurpose","Keystone 5010","","TP13"
"1","PFL_MIX","TestPoint:TestPoint_Keystone_5010-5014_Multipurpose","Keystone 5010","","TP14"
"1","+VA","TestPoint:TestPoint_Keystone_5010-5014_Multipurpose","Keystone 5010","","TP15"
"1","-VA","TestPoint:TestPoint_Keystone_5010-5014_Multipurpose","Keystone 5010","","TP16"
"1","+VBUS_R","TestPoint:TestPoint_Keystone_5010-5014_Multipurpose","Keystone 5010","","TP17"
"1","-VBUS_R","TestPoint:TestPoint_Keystone_5010-5014_Multipurpose","Keystone 5010","","TP18"
"2","GNDA","TestPoint:TestPoint_Keystone_5010-5014_Multipurpose","Keystone 5010","","TP19 TP20"
"6","OPA1612","Package_SO:SOIC-8_3.9x4.9mm_P1.27mm","TI OPA1612AIDR","","U1 U2 U3 U4 U5 U6"
"1","OPA1656","Package_SO:SOIC-8_3.9x4.9mm_P1.27mm","TI OPA1656IDR","","U7"
"1","DRV135","Package_SO:SOIC-8_3.9x4.9mm_P1.27mm","TI DRV135UA","","U8"
"1","LM393","Package_SO:SOIC-8_3.9x4.9mm_P1.27mm","TI LM393BIDR","","U9"

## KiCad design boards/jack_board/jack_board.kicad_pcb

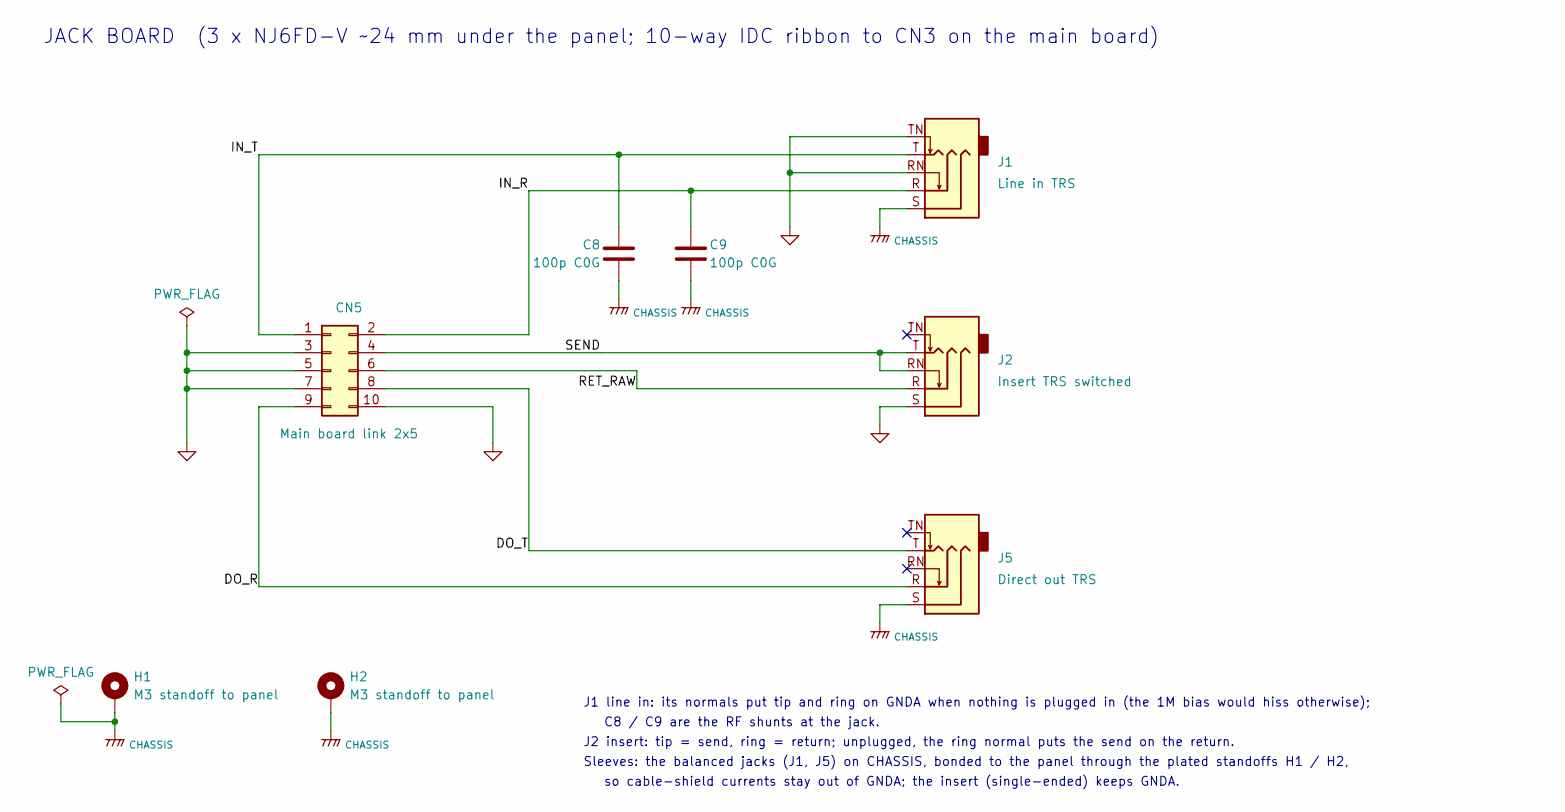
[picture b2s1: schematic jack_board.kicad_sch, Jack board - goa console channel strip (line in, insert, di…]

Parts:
C8, C9: 100p C0G; C_0805_2012Metric; MPN KEMET C0805C101J5GACTU
CN5: Main board link 2x5; IDC-Header_2x05_P2.54mm_Vertical; MPN Wurth 61201021621 (2x5 box header)
H1, H2: M3 standoff to panel; MountingHole_3.2mm_M3_Pad
J1: Line in TRS; Jack_6.35mm_Neutrik_NJ6FD-V_Vertical; MPN Neutrik NJ6FD-V
J2: Insert TRS switched; Jack_6.35mm_Neutrik_NJ6FD-V_Vertical; MPN Neutrik NJ6FD-V
J5: Direct out TRS; Jack_6.35mm_Neutrik_NJ6FD-V_Vertical; MPN Neutrik NJ6FD-V

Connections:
/CHASSIS: C8.2, C9.2, H1.1, H2.1, J1.S, J5.S
/DO_R: CN5.9, J5.R
/DO_T: CN5.8, J5.T
/IN_R: C9.1, CN5.2, J1.R
/IN_T: C8.1, CN5.1, J1.T
/RET_RAW: CN5.6, J2.R
/SEND: CN5.4, J2.RN, J2.T
GNDA: CN5.3, CN5.5, CN5.7, CN5.10, J1.RN, J1.TN, J2.S

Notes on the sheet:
JACK BOARD (3 x NJ6FD-V ~24 mm under the panel; 10-way IDC ribbon to CN3 on the main board)
J1 line in: its normals put tip and ring on GNDA when nothing is plugged in (the 1M bias would hiss otherwise);
C8 / C9 are the RF shunts at the jack.
J2 insert: tip = send, ring = return; unplugged, the ring normal puts the send on the return.
Sleeves: the balanced jacks (J1, J5) on CHASSIS, bonded to the panel through the plated standoffs H1 / H2,
so cable-shield currents stay out of GNDA; the insert (single-ended) keeps GNDA.

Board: 2 copper layers, 8 parts (3 on the bottom side), 8 nets, no tracks yet.

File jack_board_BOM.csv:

"Qty","Value","Footprint","MPN","DNP","References"
"2","100p C0G","Capacitor_SMD:C_0805_2012Metric","","","C8 C9"
"1","Main board link 2x5","Connector_IDC:IDC-Header_2x05_P2.54mm_Vertical","Wurth 61201021621 (2x5 box header)","","CN5"
"1","Line in TRS","Connector_Audio:Jack_6.35mm_Neutrik_NJ6FD-V_Vertical","Neutrik NJ6FD-V","","J1"
"1","Insert TRS switched","Connector_Audio:Jack_6.35mm_Neutrik_NJ6FD-V_Vertical","Neutrik NJ6FD-V","","J2"
"1","Direct out TRS","Connector_Audio:Jack_6.35mm_Neutrik_NJ6FD-V_Vertical","Neutrik NJ6FD-V","","J5"
